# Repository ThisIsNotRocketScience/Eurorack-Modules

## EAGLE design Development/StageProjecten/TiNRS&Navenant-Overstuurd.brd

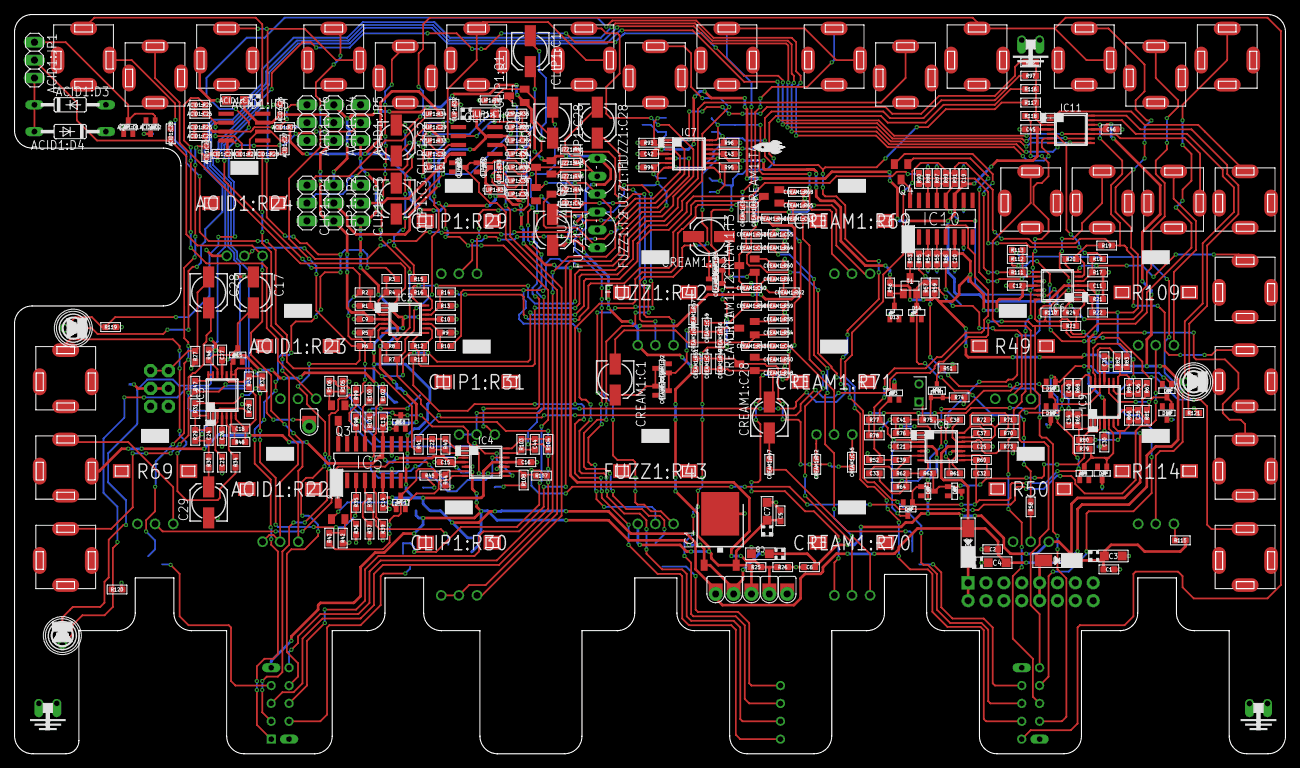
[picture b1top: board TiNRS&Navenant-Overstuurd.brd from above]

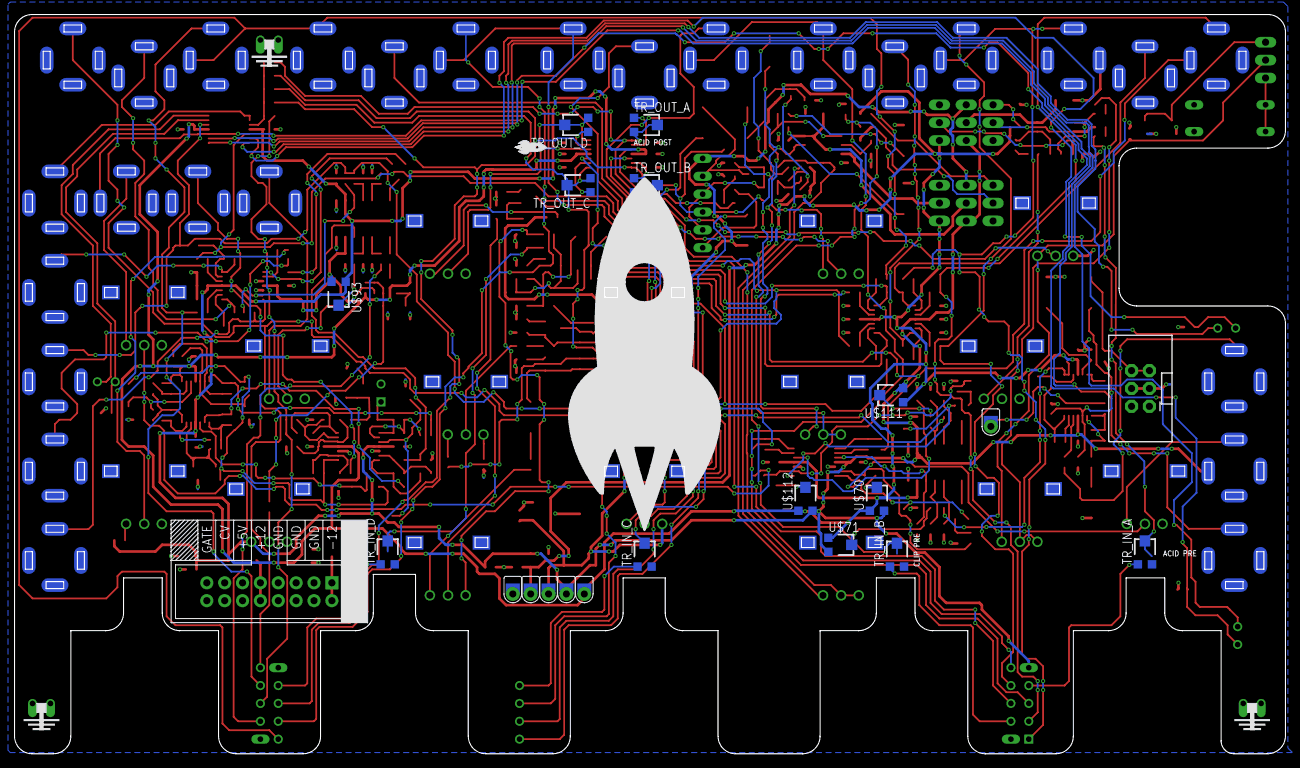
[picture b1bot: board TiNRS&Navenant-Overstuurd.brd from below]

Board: 2 copper layers, 180.7 x 105.1 mm, 375 parts (17 on the bottom side), 216 nets.

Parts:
ACID1:C7: 10uF; CASE-A_3216
ACID1:C22, ACID1:C28: 1nF; C0603
ACID1:C23: 10nF; C0603
ACID1:C24, ACID1:C25: 100n; C0603
ACID1:C26: 47nF; C0603
ACID1:C27: 1uF; C0603
ACID1:D1, ACID1:D2: BAS16W; SOT-323
ACID1:D3, ACID1:D4: 1N4148DO35-10; DO35-10
ACID1:IC5: UA741D; SO08
ACID1:JP1: GERMANIUMSELECTOR; 1X03
ACID1:JP4: ACID+; 1X03
ACID1:JP5: ACID-; 1X03
ACID1:JP6: ACIDBIAS; 1X03
ACID1:R22: 10KB; ALPS_POT_SQUAREHOLES
ACID1:R23: 1MC; ALPS_POT_SQUAREHOLES
ACID1:R24: 10KA; ALPS_POT_SQUAREHOLES
ACID1:R25: 10K; R0603
ACID1:R26: 4.7K; R0603
ACID1:R27, ACID1:R72: 1M; R0603
ACID1:R28: 5.6K; R0603
C1, C2, C5, C6, C9, C10, C11, C12, C13, C14, C15, C16, C19, C20, C21, C25, C26, C27, C30, C31, C38, C42, C43, C45, C46: 100n; C0603
C3, C4, C7, C8: 10u; CASE-A_3216
C17, C28, C29: 10uF; 153CLV-0505
C18, C22, C23, C44: 10pF; C0603
C24: 47pF; C0603
C32, C34, C35, C36, C37: 33p; C0603
C33: 220p; C0603
C39: 680n; C0603
C40, C41: 33p FIX; C0603
CLIP1:C1, CLIP1:C3: 4.7uF; 153CLV-0505
CLIP1:C2: 2.2uF; 153CLV-0505
CLIP1:C4, CLIP1:C25: 100n; C0603
CLIP1:C7: 10uF; CASE-A_3216
CLIP1:C28: 1uF; 153CLV-0505
CLIP1:C29, CLIP1:C36: 22nF; C0603
CLIP1:C30: 1nF; C0603
CLIP1:C31: 100pF; C0603
CLIP1:C35: 3.3nF; C0603
CLIP1:D1, CLIP1:D2: BAS16W; SOT-323
CLIP1:IC6: UA741D; SO08
CLIP1:JP1: CLIPBIAS; 1X03
CLIP1:JP2: CLIP+; 1X03
CLIP1:JP3: CLIP-; 1X03
CLIP1:Q1: SST201; SOT23
CLIP1:R29, CLIP1:R30, CLIP1:R31: 100KA; ALPS_POT_SQUAREHOLES
CLIP1:R32, CLIP1:R34, CLIP1:R39: 1M; R0603
CLIP1:R33, CLIP1:R37: 1K; R0603
CLIP1:R35: 560R; R0603
CLIP1:R36: 47R; R0603
CLIP1:R38: 1.5K; R0603
CLIP1:R40: 10K; R0603
CREAM1:C1, CREAM1:C2, CREAM1:C28: 1uF; 153CLV-0505
CREAM1:C44, CREAM1:C47, CREAM1:C50: 470pF; C0603
CREAM1:C45: 1uF; C0603
CREAM1:C46, CREAM1:C49, CREAM1:C53, CREAM1:C54: 100nF; C0603
CREAM1:C52: 4nF; C0603
CREAM1:C55: 10nF; C0603
CREAM1:D1, CREAM1:D2, CREAM1:D3, CREAM1:D4: BAS16W; SOT-323
CREAM1:R47, CREAM1:R63: 39K; R0603
CREAM1:R48: 47K; R0603
CREAM1:R49, CREAM1:R56, CREAM1:R61: 470K; R0603
CREAM1:R50: 100R; R0603
CREAM1:R51, CREAM1:R53, CREAM1:R57, CREAM1:R58, CREAM1:R62: 10K; R0603
CREAM1:R52: 1K; R0603
CREAM1:R54, CREAM1:R59, CREAM1:R65: 100K; R0603
CREAM1:R55, CREAM1:R60: 150R; R0603
CREAM1:R64: 22K; R0603
CREAM1:R66: 430K; R0603
CREAM1:R67: 15K; R0603
CREAM1:R68: 3.3K; R0603
CREAM1:R69, CREAM1:R70, CREAM1:R71: 100KB; ALPS_POT_SQUAREHOLES
CREAM1:T1, CREAM1:T2, CREAM1:T3, CREAM1:T4: 2n3904; SOT23-BEC
D1, D2: 1n4001; DO-214AC
D3, D4, D5, D6, D7, D8, D9, D10, D11, D12, D13, D14, D15, D17, D18: BAS16W; SOT-323
D16, D19, D20: 3MMLED
FUZZ1:C1: 20uF; 153CLV-0505
FUZZ1:C28: 2.2uF; 153CLV-0505
FUZZ1:C42: 10nF; C0603
FUZZ1:Q1, FUZZ1:Q2: MMBT3906LT1SMD; SOT23-BEC
FUZZ1:R41: 100K; R0603
FUZZ1:R42: 500KA; ALPS_POT_SQUAREHOLES
FUZZ1:R43: 1KB; ALPS_POT_SQUAREHOLES
FUZZ1:R44: 8.2K; R0603
FUZZ1:R45: 33K; R0603
FUZZ1:R46: 470R; R0603
FUZZ1:T1, FUZZ1:T2: TO92-EBC
IC1: 7809DT; TO252
IC2, IC3, IC4, IC6, IC7, IC8, IC9, IC11: TL074TSSOP14; TSSOP14
IC5, IC10: LM13700M; SO16
J1, J3, J4, J5, J6, J7, J8, J9, J10, J11, J12, J13, J14, J15, J16, J17, J18, J19, J20, J21, J22, J23, J24, J25, J26, J27: JACK; 3.5MM-JACK-SWITCH-13MM-NOHOLES
J2: POWERSHROUDED; POWER_16_SHROUDED
PCB1: EURORACK_PCB5STOMP; EURORACK36HP_5STOMP
Q1, Q3, Q4: MMBT3906LT1SMD; SOT23-BEC
R1, R2, R3, R4, R5, R6, R7, R8, R9, R10, R11, R12, R13, R14, R15, R16, R17, R18, R19, R20, R21, R22, R23, R24, R25, R26, R34, R48: 100k; R0603
R27: 1M; R0603
R28: 150K; R0603
R29, R42, R60, R72, R74, R105: 10K; R0603
R30: 470R; R0603
R31, R41, R47, R104: 1K; R0603
R32, R33, R38, R39, R40, R43, R44, R64, R65, R66, R67, R68, R71, R76, R78, R80, R83, R84, R92, R97, R101, R102, R103, R106, R107, R116, R117, R118: 100K; R0603
R35, R98: 4.7K; R0603
R36, R37, R99, R100: 10R; R0603
R45, R46, R108: 330K; R0603
R49, R69, R109: 100KB; ALPS_POT_SQUAREHOLES
R50, R114: 10KB; ALPS_POT_SQUAREHOLES
R51: 14; R0603
R52, R56: 470K; R0603
R53: 4K7; R0603
R54, R55, R70: 100; R0603
R57: 22K; R0603
R58, R62, R63, R77, R79, R81, R82: 33K; R0603
R59: 4M7; R0603
R61: 47K; R0603
R73: 220K; R0603
R75: 6K8; R0603
R85: 27k; R0603
R86: 150k; R0603
R87, R88: 1k; R0603
R89, R90: 200k; R0603
R91, R110: 47k; R0603
R93, R94, R95, R96: 4.7k; R0603
R111: 2.2k; R0603
R112, R113: 18k; R0603
R115: 14k; R0603
R119, R120, R121: 1.2K; R0603
T1: 3906; SOT23-BEC
TR_IN_A: 50k; TC33X
TR_IN_B: 50k; TC33X
TR_IN_C: 50k; TC33X
TR_IN_D: 50k; TC33X
TR_OUT_A: 50k; TC33X
TR_OUT_B: 50k; TC33X
TR_OUT_C: 50k; TC33X
TR_OUT_D: 50k; TC33X
U$13, U$15, U$41, U$42, U$43, U$44: VOLTAGETESTPAD; POWERTESTPAD
U$22: 5STOMPBOARD; BYPASSBOARD
U$23: HEADPHONEHOLE_BIGGAP; HEADPHONEHOLE_GAP
U$48, U$49, U$50: GNDLOOP; GROUNDLOOP
U$68: HEADPHONE; 2X3-SHROUDED
U$70, U$71, U$111, U$112: 100k; TC33X
U$74: BAT54S; SOT23
U$92: TESTPOINT_DUAL_PTH; TESTPAD_DUAL_PTH
U$93: 50K; TC33X
U$94, U$95: TINRS_ARTWORKTINYDATE; JUSTATINYROCKET_DATECODE
U$96: ROCKET-5CM

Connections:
4.5V: ACID1:R72.2, CLIP1:R34.2, R25.1, R26.2, U$44.P$1, U$44.P$2, U$44.P$3
9V: ACID1:JP4.1, C5.2, C7.+, CLIP1:JP2.1, CLIP1:Q1.1, CREAM1:R51.1, CREAM1:R57.1, CREAM1:R62.1, CREAM1:R66.2, CREAM1:R67.2, FUZZ1:C1.+, FUZZ1:Q1.E, FUZZ1:R42.P$1, FUZZ1:R43.P$1, FUZZ1:T1.E, IC1.2, R25.2, U$42.P$1, U$42.P$2, U$42.P$3
12V: ACID1:JP4.3, C1.2, C3.+, C6.2, C8.+, C9.2, C11.2, C13.2, C15.2, C19.2, C21.2, C26.2, C30.2, C42.2, C45.2, CLIP1:JP2.3, D1.2, IC1.1, IC2.4, IC3.4, IC4.4, IC5.11, IC6.4, IC7.4, IC8.4, IC9.4, IC10.11, IC11.4, J21.SWITCH_B@1, J21.SWITCH_T@3, R50.P$3, R115.1, U$13.P$1, U$13.P$2, U$13.P$3, U$22.12V, U$70.3, U$71.3, U$93.1, U$111.3, U$112.3
-12V: ACID1:JP5.3, C2.1, C4.-, C10.1, C12.1, C14.1, C16.1, C20.1, C25.1, C27.1, C31.1, C43.1, C46.1, CLIP1:JP3.3, D2.1, IC2.11, IC3.11, IC4.11, IC5.6, IC6.11, IC7.11, IC8.11, IC9.11, IC10.6, IC11.11, R56.2, R59.1, U$41.P$1, U$41.P$2, U$41.P$3, U$70.1, U$71.1, U$93.3, U$111.1, U$112.1
ACID1:ACIDNE: ACID1:C24.1, ACID1:IC5.4, ACID1:JP5.2
ACID1:ACIDPL: ACID1:C7.+, ACID1:C25.1, ACID1:IC5.7, ACID1:JP4.2
ACID1:ACIDVI: ACID1:IC5.3, ACID1:JP6.2, ACID1:R25.1
ACID1:N$2: ACID1:D3.C, ACID1:D4.A, ACID1:JP1.3
ACID1:N$3: ACID1:D1.CATHODE, ACID1:D2.ANODE, ACID1:JP1.1
ACID1:N$20: ACID1:C23.2, ACID1:R25.2
ACID1:N$22: ACID1:C26.2, ACID1:IC5.2, ACID1:R27.1
ACID1:N$23: ACID1:C26.1, ACID1:R26.1
ACID1:N$32: ACID1:C27.1, ACID1:IC5.6, ACID1:R27.2
ACID1:N$33: ACID1:R23.P$3, ACID1:R26.2
ACID1:N$34: ACID1:C28.2, ACID1:JP1.2, ACID1:R22.P$3, ACID1:R24.P$3
ACID1:N$35: ACID1:C27.2, ACID1:R28.2
ACID1:N$36: ACID1:R22.P$1, ACID1:R22.P$2, ACID1:R28.1
ACID1:TO4.5V: ACID1:JP6.1, ACID1:R72.1
BIASINPUT: J23.TIP_B@1, J23.TIP_T@3, R61.2
BIASMAINLINE: C32.1, D4.ANODE, D6.ANODE, D8.ANODE, D9.ANODE, D10.ANODE, IC8.8, R60.1
CLIP1:CLIPNE: CLIP1:C4.1, CLIP1:IC6.4, CLIP1:JP3.2
CLIP1:CLIPPL: CLIP1:C7.+, CLIP1:C25.1, CLIP1:IC6.7, CLIP1:JP2.2
CLIP1:CLIPVI: CLIP1:C29.2, CLIP1:JP1.2, CLIP1:R33.1
CLIP1:N$38: CLIP1:C30.2, CLIP1:IC6.3, CLIP1:R33.2
CLIP1:N$41: CLIP1:JP1.1, CLIP1:R34.1
CLIP1:N$42: CLIP1:C31.1, CLIP1:IC6.2, CLIP1:R31.P$1, CLIP1:R31.P$2, CLIP1:R35.2, CLIP1:R36.2
CLIP1:N$43: CLIP1:C1.+, CLIP1:C31.2, CLIP1:IC6.6, CLIP1:R31.P$3
CLIP1:N$44: CLIP1:C1.-, CLIP1:R37.1
CLIP1:N$45: CLIP1:D1.CATHODE, CLIP1:D2.ANODE, CLIP1:R30.P$1, CLIP1:R30.P$2, CLIP1:R37.2
CLIP1:N$46: CLIP1:R30.P$3, CLIP1:R38.1
CLIP1:N$47: CLIP1:C2.+, CLIP1:R36.1
CLIP1:N$48: CLIP1:C3.+, CLIP1:R35.1
CLIP1:N$49: CLIP1:C35.1, CLIP1:C36.1, CLIP1:R38.2
CLIP1:N$50: CLIP1:C36.2, CLIP1:Q1.3, CLIP1:R39.2
CLIP1:N$51: CLIP1:C28.+, CLIP1:Q1.2, CLIP1:R40.2
CLIP1:N$52: CLIP1:C28.-, CLIP1:R29.P$3
CREAM1:N$1: CREAM1:C28.-, CREAM1:R47.2
CREAM1:N$61: CREAM1:C28.+, CREAM1:C44.1, CREAM1:R48.2, CREAM1:R49.2, CREAM1:T1.B
CREAM1:N$62: CREAM1:R50.1, CREAM1:T1.E
CREAM1:N$63: CREAM1:C44.2, CREAM1:C45.1, CREAM1:R49.1, CREAM1:R51.2, CREAM1:T1.C
CREAM1:N$64: CREAM1:C45.2, CREAM1:R71.P$3
CREAM1:N$65: CREAM1:C1.-, CREAM1:C47.1, CREAM1:R53.2, CREAM1:R54.2, CREAM1:R56.2, CREAM1:T2.B
CREAM1:N$66: CREAM1:C1.+, CREAM1:D1.ANODE, CREAM1:D2.CATHODE
CREAM1:N$67: CREAM1:R55.2, CREAM1:T2.E
CREAM1:N$68: CREAM1:C47.2, CREAM1:C49.1, CREAM1:D1.CATHODE, CREAM1:D2.ANODE, CREAM1:R56.1, CREAM1:R57.2, CREAM1:T2.C
CREAM1:N$69: CREAM1:C49.2, CREAM1:R58.1
CREAM1:N$70: CREAM1:C2.-, CREAM1:C50.1, CREAM1:R58.2, CREAM1:R59.2, CREAM1:R61.2, CREAM1:T3.B
CREAM1:N$71: CREAM1:R60.2, CREAM1:T3.E
CREAM1:N$72: CREAM1:C50.2, CREAM1:C52.1, CREAM1:D3.ANODE, CREAM1:D4.CATHODE, CREAM1:R61.1, CREAM1:R62.2, CREAM1:R63.1, CREAM1:T3.C
CREAM1:N$73: CREAM1:C53.1, CREAM1:R70.P$2
CREAM1:N$74: CREAM1:C55.2, CREAM1:R63.2, CREAM1:R70.P$1
CREAM1:N$75: CREAM1:C52.2, CREAM1:R64.1, CREAM1:R70.P$3
CREAM1:N$76: CREAM1:C2.+, CREAM1:D3.CATHODE, CREAM1:D4.ANODE
CREAM1:N$77: CREAM1:C53.2, CREAM1:R65.2, CREAM1:R66.1, CREAM1:T4.B
CREAM1:N$78: CREAM1:C54.1, CREAM1:R67.1, CREAM1:T4.C
CREAM1:N$79: CREAM1:R68.2, CREAM1:T4.E
CREAM1:N$80: CREAM1:C54.2, CREAM1:R69.P$3
CREAM1:N$84: CREAM1:R52.1, CREAM1:R71.P$1
CREAM1:N$85: CREAM1:C46.2, CREAM1:R53.1
CREAM1:N$86: CREAM1:C46.1, CREAM1:R71.P$2
CROSSFADER_OUT: IC6.14, J26.TIP_B@1, J26.TIP_T@3, R110.1
CV_IN: J25.TIP_B@1, J25.TIP_T@3, R112.2
ENVELOPE_OUT: IC11.10, J1.SWITCH_B@1, J1.SWITCH_T@3, J24.TIP_B@1, J24.TIP_T@3, R47.1
EURORACK_IN: J20.TIP_B@1, J20.TIP_T@3, R34.1
FUZZ1:N$53: FUZZ1:Q2.E, FUZZ1:R41.1, FUZZ1:R43.P$3, FUZZ1:T2.E
FUZZ1:N$54: FUZZ1:C28.-, FUZZ1:Q1.B, FUZZ1:R41.2, FUZZ1:T1.B
FUZZ1:N$55: FUZZ1:Q1.C, FUZZ1:Q2.B, FUZZ1:R45.2, FUZZ1:T1.C, FUZZ1:T2.B
FUZZ1:N$56: FUZZ1:C1.-, FUZZ1:R43.P$2
FUZZ1:N$57: FUZZ1:C42.2, FUZZ1:R42.P$3
FUZZ1:N$58: FUZZ1:C42.1, FUZZ1:R44.1, FUZZ1:R46.2
FUZZ1:N$59: FUZZ1:Q2.C, FUZZ1:R44.2, FUZZ1:T2.C
GND: ACID1:C7.-, ACID1:C22.2, ACID1:C24.2, ACID1:C25.2, ACID1:C28.1, ACID1:D1.ANODE, ACID1:D2.CATHODE, ACID1:D3.A, ACID1:D4.C, ACID1:JP5.1, ACID1:R23.P$1, ACID1:R23.P$2, ACID1:R24.P$1, C1.1, C2.2, C3.-, C4.+, C5.1, C6.1, C7.-, C8.-, C9.1, C10.2, C11.1, C12.2, C13.1, C14.2, C15.1, C16.2, C17.-, C19.1, C20.2, C21.1, C23.1, C25.2, C26.1, C27.2, C29.-, C30.1, C31.2, C42.1, C43.2, C45.1, C46.2, CLIP1:C2.-, CLIP1:C3.-, CLIP1:C4.2, CLIP1:C7.-, CLIP1:C25.2, CLIP1:C30.1, CLIP1:C35.2, CLIP1:D1.ANODE, CLIP1:D2.CATHODE, CLIP1:JP3.1, CLIP1:R29.P$1, CLIP1:R32.2, CLIP1:R39.1, CLIP1:R40.1, CREAM1:C55.1, CREAM1:R48.1, CREAM1:R50.2, CREAM1:R52.2, CREAM1:R54.1, CREAM1:R55.1, CREAM1:R59.1, CREAM1:R60.1, CREAM1:R64.2, CREAM1:R65.1, CREAM1:R68.1, CREAM1:R69.P$1, D3.CATHODE, D5.CATHODE, D7.CATHODE, D11.CATHODE, D12.CATHODE, D13.ANODE, D14.ANODE, FUZZ1:R45.1, FUZZ1:R46.1, IC1.3, IC4.5, IC4.10, IC5.7, IC5.10, IC6.10, IC6.12, IC8.5, IC8.10, IC10.7, IC10.10, J1.RING_B@1, J1.RING_T@3, J2.3, J2.4, J2.5, J2.6, J2.7, J2.8, J3.RING_B@1, J3.RING_T@3, J4.RING_B@1, J4.RING_T@3, J5.RING_B@1, J5.RING_T@3, J6.RING_B@1, J6.RING_T@3, J7.RING_B@1, J7.RING_T@3, J8.RING_B@1, J8.RING_T@3, J9.RING_B@1, J9.RING_T@3, J10.RING_B@1, J10.RING_T@3, J11.RING_B@1, J11.RING_T@3, J12.RING_B@1, J12.RING_T@3, J13.RING_B@1, J13.RING_T@3, J14.RING_B@1, J14.RING_T@3, J15.RING_B@1, J15.RING_T@3, J16.RING_B@1, J16.RING_T@3, J17.RING_B@1, J17.RING_T@3, J18.RING_B@1, J18.RING_T@3, J19.RING_B@1, J19.RING_T@3, J20.RING_B@1, J20.RING_T@3, J20.SWITCH_B@1, J20.SWITCH_T@3, J21.RING_B@1, J21.RING_T@3, J22.RING_B@1, J22.RING_T@3, J23.RING_B@1, J23.RING_T@3, J23.SWITCH_B@1, J23.SWITCH_T@3, J24.RING_B@1, J24.RING_T@3, J25.RING_B@1, J25.RING_T@3, J25.SWITCH_B@1, J25.SWITCH_T@3, J26.RING_B@1, J26.RING_T@3, J27.RING_B@1, J27.RING_T@3, R1.2, R5.2, R9.2, R13.2, R17.2, R21.2, R26.1, R27.1, R28.1, R36.1, R37.2, R39.2, R42.1, R46.1, R49.P$1, R50.P$1, R51.2, R52.2, R54.1, R55.1, R69.P$1, R72.2, R73.1, R74.1, R87.1, R88.1, R93.2, R94.2, R95.2, R96.2, R99.1, R100.2, R102.2, R105.1, R109.P$1, R114.P$1, R119.1, R120.1, R121.1, TR_IN_A.3, TR_IN_B.3, TR_IN_C.3, TR_IN_D.3, U$22.GND, U$22.GND2, U$22.GND3, U$43.P$1, U$43.P$2, U$43.P$3, U$48.P$1, U$48.P$2, U$49.P$1, U$49.P$2, U$50.P$1, U$50.P$2, U$68.3, U$68.4, U$92.P$2
GUITAR_IN: C28.-, R27.2, U$68.5, U$68.6
GUITAR_OUT: R31.2, R32.2, U$15.P$1, U$15.P$2, U$15.P$3
INPUT_A: J6.TIP_B@1, J6.TIP_T@3, R2.2, U$22.P$3
INPUT_B: J4.TIP_B@1, J4.TIP_T@3, R6.2, U$22.P$7
INPUT_C: J11.TIP_B@1, J11.TIP_T@3, R10.2, U$22.P$11
INPUT_D: J14.TIP_B@1, J14.TIP_T@3, R14.2, U$22.P$15
INPUT_E: J17.TIP_B@1, J17.TIP_T@3, R22.2, U$22.P$19
INPUT_WS: R85.2, U$22.P$20
MIX_OUT: D15.ANODE, IC3.8, IC3.9, R35.1
unnamed: IC7.2, R93.1, TR_OUT_A.1
unnamed: D1.1, J2.9, J2.10
unnamed: D2.2, J2.1, J2.2
unnamed: IC11.1, IC11.2, J27.TIP_B@1, J27.TIP_T@3
unnamed: TR_IN_A.1, U$22.P$4
unnamed: ACID1:R24.P$2, IC7.3
unnamed: TR_IN_B.1, U$22.P$8
unnamed: TR_IN_C.1, U$22.P$12
unnamed: FUZZ1:C28.+, TR_IN_C.2
unnamed: IC11.3, R92.2, R97.2, R116.2, R117.2, R118.2
unnamed: IC7.9, R95.1, TR_OUT_C.1
unnamed: CLIP1:C29.1, CLIP1:R32.1, TR_IN_B.2
unnamed: D16.+, IC11.6, R119.2
unnamed: C23.2, C28.+, IC3.3, R28.2
unnamed: IC2.3, R1.1, R2.1
unnamed: IC6.9, R111.2, R112.1, R113.1
unnamed: C24.1, IC3.1, R29.2, R31.1
unnamed: IC2.1, J8.TIP_B@1, J8.TIP_T@3, R4.1
unnamed: IC2.5, R5.1, R6.1
unnamed: IC2.6, R7.1, R8.2
unnamed: Q4.E, R111.1
unnamed: IC6.8, Q4.B
unnamed: IC2.7, J5.TIP_B@1, J5.TIP_T@3, R8.1
unnamed: IC2.10, R9.1, R10.1
unnamed: IC2.9, R11.1, R12.2
unnamed: R114.P$3, R115.2
unnamed: R113.2, R114.P$2
unnamed: IC2.8, J12.TIP_B@1, J12.TIP_T@3, R12.1
unnamed: IC2.12, R13.1, R14.1
unnamed: IC2.13, R15.1, R16.2
unnamed: IC7.6, R94.1, TR_OUT_B.1
unnamed: D16.-, IC11.7
unnamed: IC2.14, J15.TIP_B@1, J15.TIP_T@3, R16.1
unnamed: IC6.5, R17.1, R18.1
unnamed: IC6.6, R19.1, R20.2
unnamed: D19.+, IC11.9, R120.2
unnamed: CLIP1:R29.P$2, IC7.5
unnamed: IC6.7, J10.TIP_B@1, J10.TIP_T@3, R20.1
unnamed: IC6.3, R21.1, R22.1
unnamed: IC6.2, R23.1, R24.2
unnamed: ACID1:C22.1, ACID1:C23.1, TR_IN_A.2
unnamed: D19.-, IC11.8
unnamed: IC6.1, J18.TIP_B@1, J18.TIP_T@3, R24.1
unnamed: C24.2, IC3.2, R29.1, R30.2
unnamed: C29.+, R30.1
unnamed: C18.2, IC3.7, R33.2, R48.2
unnamed: IC3.5, R34.2
unnamed: IC5.4, R37.1, R38.1
unnamed: IC5.3, R35.2, R36.2
unnamed: IC4.3, IC5.5, R39.1
unnamed: C22.1, IC4.2, R40.1
unnamed: C22.2, IC4.1, R40.2, R41.1
unnamed: R38.2, U$71.2
unnamed: D17.ANODE, IC4.7, Q1.B
unnamed: D17.CATHODE, IC4.6, R43.1, R44.2, R45.2
unnamed: Q1.E, R42.2, R43.2
unnamed: IC5.1, Q1.C
unnamed: R45.1, U$70.2
unnamed: R44.1, R69.P$2
unnamed: IC3.13, IC3.14, R47.2
unnamed: C17.+, D15.CATHODE, IC3.12, R46.2
unnamed: C18.1, IC3.6, R48.1
unnamed: R51.1, U$74.P$3
unnamed: C32.2, IC8.9, R60.2, R61.1
unnamed: R49.P$2, R57.2
unnamed: J22.TIP_B@1, J22.TIP_T@3, R49.P$3
unnamed: D14.CATHODE, R57.1, R58.1, R59.2, T1.E
unnamed: R50.P$2, R58.2
unnamed: C38.2, R74.2, R75.2, U$74.P$1, U$74.P$2
unnamed: C33.1, IC8.7, R62.1, R63.2, R64.2
unnamed: C33.2, C39.2, IC8.6, R62.2
unnamed: C39.1, IC10.5, R52.1
unnamed: D5.ANODE, D6.CATHODE, IC9.3, R63.1
unnamed: C34.1, IC9.1, R65.1, R79.2, R80.2
unnamed: D7.ANODE, D8.CATHODE, IC9.5, R79.1
unnamed: C34.2, IC9.2, R64.1, R65.2
unnamed: C35.2, IC9.6, R66.2, R80.1
unnamed: C35.1, IC9.7, R66.1, R67.2, R81.2
unnamed: D9.CATHODE, D12.ANODE, IC9.10, R81.1
unnamed: C36.1, IC9.8, R82.2, R83.2, R84.1
unnamed: C36.2, IC9.9, R67.1, R84.2
unnamed: D10.CATHODE, D11.ANODE, IC9.12, R82.1
unnamed: C40.2, IC9.13, R68.2, R83.1
unnamed: C40.1, IC9.14, R68.1, R77.1, R78.1
unnamed: D3.ANODE, D4.CATHODE, IC8.3, R77.2
unnamed: C41.2, IC8.2, R76.1, R78.2
unnamed: C41.1, IC8.1, R75.1, R76.2, U$92.P$1
unnamed: C38.1, IC8.12, R73.2
unnamed: C37.1, IC8.14, R70.2
unnamed: C37.2, IC8.13, R71.2, R72.1
unnamed: D13.CATHODE, R56.1, T1.B
unnamed: R53.1, T1.C
unnamed: IC10.1, R53.2
unnamed: IC10.3, R54.2, R85.1
unnamed: R86.2, U$93.2
unnamed: IC10.4, R55.2, R86.1
unnamed: IC10.13, R87.2, R89.1
unnamed: IC10.14, R88.2, R90.1
unnamed: TR_IN_D.1, U$22.P$16
unnamed: CREAM1:R47.1, TR_IN_D.2
unnamed: IC7.13, R96.1, TR_OUT_D.1
unnamed: CREAM1:R69.P$2, IC7.12
unnamed: FUZZ1:R42.P$2, IC7.10
unnamed: D20.+, IC11.13, R121.2
unnamed: D20.-, IC11.14
unnamed: IC5.13, R100.1, R101.1
unnamed: IC5.14, R98.2, R99.2
unnamed: IC4.12, IC5.12, R102.1
unnamed: C44.1, IC4.13, R103.1
unnamed: C44.2, IC4.14, R103.2, R104.1
unnamed: R101.2, U$111.2
unnamed: D18.ANODE, IC4.8, Q3.B
unnamed: D18.CATHODE, IC4.9, R106.1, R107.2, R108.2
unnamed: Q3.E, R105.2, R106.2
unnamed: IC5.16, Q3.C
unnamed: R108.1, U$112.2
unnamed: R107.1, R109.P$2
unnamed: IC2.2, R3.1, R4.2
OPAMP_A: IC7.1, R92.1, TR_OUT_A.2, TR_OUT_A.3, U$22.P$2
OPAMP_B: IC7.7, R97.1, TR_OUT_B.2, TR_OUT_B.3, U$22.P$6
OPAMP_C: IC7.8, R116.1, TR_OUT_C.2, TR_OUT_C.3, U$22.P$10
OPAMP_D: IC7.14, R117.1, TR_OUT_D.2, TR_OUT_D.3, U$22.P$14
OTA_CONTROL: IC10.16, Q4.C
OTA_OUT: IC6.13, IC10.12, R91.2, R110.2
OUTPUT_A: J4.SWITCH_B@1, J4.SWITCH_T@3, J7.TIP_B@1, J7.TIP_T@3, R3.2, U$22.P$1
OUTPUT_B: J9.TIP_B@1, J9.TIP_T@3, J11.SWITCH_B@1, J11.SWITCH_T@3, R7.2, U$22.P$5
OUTPUT_C: J13.TIP_B@1, J13.TIP_T@3, J14.SWITCH_B@1, J14.SWITCH_T@3, R11.2, U$22.P$9
OUTPUT_D: J16.TIP_B@1, J16.TIP_T@3, J17.SWITCH_B@1, J17.SWITCH_T@3, R15.2, U$22.P$13
OUTPUT_E: J19.TIP_B@1, J19.TIP_T@3, R23.2, R98.1, U$22.P$17
OUTPUT_WS: R70.1, R71.1, R118.1, U$22.P$18
VCA_CV_IN1: J21.TIP_B@1, J21.TIP_T@3, R69.P$3
VCA_CV_IN2: J1.TIP_B@1, J1.TIP_T@3, R109.P$3
VCA_OUTPUT1: IC11.5, J6.SWITCH_B@1, J6.SWITCH_T@3, R18.2, R41.2, R90.2
VCA_OUTPUT2: IC11.12, J3.TIP_B@1, J3.TIP_T@3, R19.2, R89.2, R91.1, R104.2
VCA_SIG_IN: IC3.10, R32.1, R33.1

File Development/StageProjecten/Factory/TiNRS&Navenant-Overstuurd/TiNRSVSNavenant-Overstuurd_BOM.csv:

Comment,Designator,Footprint,LCSC Part #
100n,"C1, C2, C5, C6, ACID1:C24, ACID1:C25, C9, C10, C11, C12, C26, C27, C13, C14, C15, C16, C19, C20, C21, C25, C30, C31, C38, CLIP1:C4, CLIP1:C25, C42, C43, C45, C46",C0603,
1nF,"ACID1:C22, ACID1:C28, CLIP1:C30",C0603,
10nF,"ACID1:C23, FUZZ1:C42, CREAM1:C55",C0603,
47nF,"ACID1:C26",C0603,
1uF,"ACID1:C27, CREAM1:C45",C0603,
470pF,"CREAM1:C44, CREAM1:C47, CREAM1:C50",C0603,
100nF,"CREAM1:C46, CREAM1:C49, CREAM1:C53, CREAM1:C54",C0603,
4nF,"CREAM1:C52",C0603,
22nF,"CLIP1:C29, CLIP1:C36",C0603,
100pF,"CLIP1:C31",C0603,
3.3nF,"CLIP1:C35",C0603,
10pF,"C23, C22, C18, C44",C0603,
47pF,"C24",C0603,
33p,"C32, C34, C35, C36, C37",C0603,
220p,"C33",C0603,
680n,"C39",C0603,
33p FIX,"C40, C41",C0603,
10u,"C3, C4, C7, C8",CASE-A_3216,
10uF,"ACID1:C7, CLIP1:C7",CASE-A_3216,
1n4001,"D1, D2",DO-214AC,
UA741D,"ACID1:IC5, CLIP1:IC6",SO08,
ACID+,"ACID1:JP4",1X03,
ACID-,"ACID1:JP5",1X03,
CLIPBIAS,"CLIP1:JP1",1X03,
CLIP+,"CLIP1:JP2",1X03,
CLIP-,"CLIP1:JP3",1X03,
ACIDBIAS,"ACID1:JP6",1X03,
GERMANIUMSELECTOR,"ACID1:JP1",1X03,
10KB,"ACID1:R22, R50, R114",ALPS_POT_SQUAREHOLES,
1MC,"ACID1:R23",ALPS_POT_SQUAREHOLES,
10KA,"ACID1:R24",ALPS_POT_SQUAREHOLES,
500KA,"FUZZ1:R42",ALPS_POT_SQUAREHOLES,
1KB,"FUZZ1:R43",ALPS_POT_SQUAREHOLES,
100KB,"CREAM1:R69, CREAM1:R70, CREAM1:R71, R69, R109, R49",ALPS_POT_SQUAREHOLES,
100KA,"CLIP1:R29, CLIP1:R30, CLIP1:R31",ALPS_POT_SQUAREHOLES,
10K,"ACID1:R25, CREAM1:R51, CREAM1:R53, CREAM1:R57, CREAM1:R58, CREAM1:R62, CLIP1:R40, R29, R42, R105, R60, R72, R74",R0603,
4.7K,"ACID1:R26, R35, R98",R0603,
1M,"ACID1:R27, CLIP1:R32, CLIP1:R34, CLIP1:R39, ACID1:R72, R27",R0603,
5.6K,"ACID1:R28",R0603,
100K,"FUZZ1:R41, CREAM1:R54, CREAM1:R59, CREAM1:R65, R32, R33, R38, R39, R40, R43, R44, R101, R102, R103, R106, R107, R64, R65, R66, R67, R68, R71, R76, R78, R80, R83, R84, R92, R97, R116, R117, R118",R0603,
8.2K,"FUZZ1:R44",R0603,
33K,"FUZZ1:R45, R58, R62, R63, R77, R79, R81, R82",R0603,
470R,"FUZZ1:R46, R30",R0603,
39K,"CREAM1:R47, CREAM1:R63",R0603,
47K,"CREAM1:R48, R61",R0603,
470K,"CREAM1:R49, CREAM1:R56, CREAM1:R61, R52, R56",R0603,
100R,"CREAM1:R50",R0603,
1K,"CREAM1:R52, CLIP1:R33, CLIP1:R37, R31, R41, R47, R104",R0603,
150R,"CREAM1:R55, CREAM1:R60",R0603,
22K,"CREAM1:R64, R57",R0603,
430K,"CREAM1:R66",R0603,
15K,"CREAM1:R67",R0603,
3.3K,"CREAM1:R68",R0603,
560R,"CLIP1:R35",R0603,
47R,"CLIP1:R36",R0603,
1.5K,"CLIP1:R38",R0603,
100k,"R1, R2, R3, R4, R5, R6, R7, R8, R9, R10, R11, R12, R13, R14, R15, R16, R17, R18, R19, R20, R21, R22, R23, R24, R25, R26, R34, R48",R0603,
150K,"R28",R0603,
10R,"R36, R37, R99, R100",R0603,
330K,"R45, R46, R108",R0603,
14,"R51",R0603,
4K7,"R53",R0603,
100,"R54, R55, R70",R0603,
4M7,"R59",R0603,
220K,"R73",R0603,
6K8,"R75",R0603,
27k,"R85",R0603,
150k,"R86",R0603,
1k,"R87, R88",R0603,
200k,"R89, R90",R0603,
47k,"R91, R110",R0603,
2.2k,"R111",R0603,
18k,"R112, R113",R0603,
14k,"R115",R0603,
4.7k,"R93, R94, R95, R96",R0603,
1.2K,"R119, R120, R121",R0603,
20uF,"FUZZ1:C1",153CLV-0505,
2.2uF,"FUZZ1:C28, CLIP1:C2",153CLV-0505,
1uF,"CREAM1:C1, CREAM1:C2, CREAM1:C28, CLIP1:C28",153CLV-0505,
4.7uF,"CLIP1:C1, CLIP1:C3",153CLV-0505,
10uF,"C28, C29, C17",153CLV-0505,
MMBT3906LT1SMD,"FUZZ1:Q1, FUZZ1:Q2, Q1, Q3, Q4",SOT23-BEC,
7809DT,"IC1",TO252,
JACK,"J10, J11, J12, J13, J14, J15, J16, J3, J4, J5, J6, J7, J8, J9, J17, J18, J19, J20, J21, J22, J23, J25, J26, J1, J24, J27",3.5MM-JACK-SWITCH-13MM-NOHOLES,
POWERSHROUDED,"J2",POWER_16_SHROUDED,
2n3904,"CREAM1:T1, CREAM1:T2, CREAM1:T3, CREAM1:T4",SOT23-BEC,
EURORACK_PCB5STOMP,"PCB1",EURORACK36HP_5STOMP,
SST201,"CLIP1:Q1",SOT23,
VOLTAGETESTPAD,"U$13, U$41, U$42, U$43, U$44, U$15",POWERTESTPAD,
5STOMPBOARD,"U$22",BYPASSBOARD,
BAS16W,"CREAM1:D1, CREAM1:D2, CREAM1:D3, CREAM1:D4, CLIP1:D1, CLIP1:D2, D3, D4, D5, D6, D7, D8, D9, D10, D11, D12, D13, D14, ACID1:D1, ACID1:D2, D15, D17, D18",SOT-323,
TL074TSSOP14,"IC2, IC6, IC3, IC4, IC8, IC9, IC7, IC11",TSSOP14,
GNDLOOP,"U$48, U$49, U$50",GROUNDLOOP,
LM13700M,"IC5, IC10",SO16,
HEADPHONE,"U$68",2X3-SHROUDED,
100k,"U$70, U$71, U$111, U$112",TC33X,
50K,"U$93",TC33X,
50k,"TR_OUT_A, TR_IN_A, TR_OUT_B, TR_IN_B, TR_OUT_C, TR_IN_C, TR_OUT_D, TR_IN_D",TC33X,
HEADPHONEHOLE_BIGGAP,"U$23",HEADPHONEHOLE_GAP,
BAT54S,"U$74",SOT23,
3906,"T1",SOT23-BEC,
TESTPOINT_DUAL_PTH,"U$92",TESTPAD_DUAL_PTH,
1N4148DO35-10,"ACID1:D3, ACID1:D4",DO35-10,
,"FUZZ1:T1, FUZZ1:T2",TO92-EBC,
,"D16, D19, D20",3MMLED,
TINRS_ARTWORKTINYDATE,"U$94, U$95",JUSTATINYROCKET_DATECODE,
ROCKET-5CM,"U$96",ROCKET-5CM,

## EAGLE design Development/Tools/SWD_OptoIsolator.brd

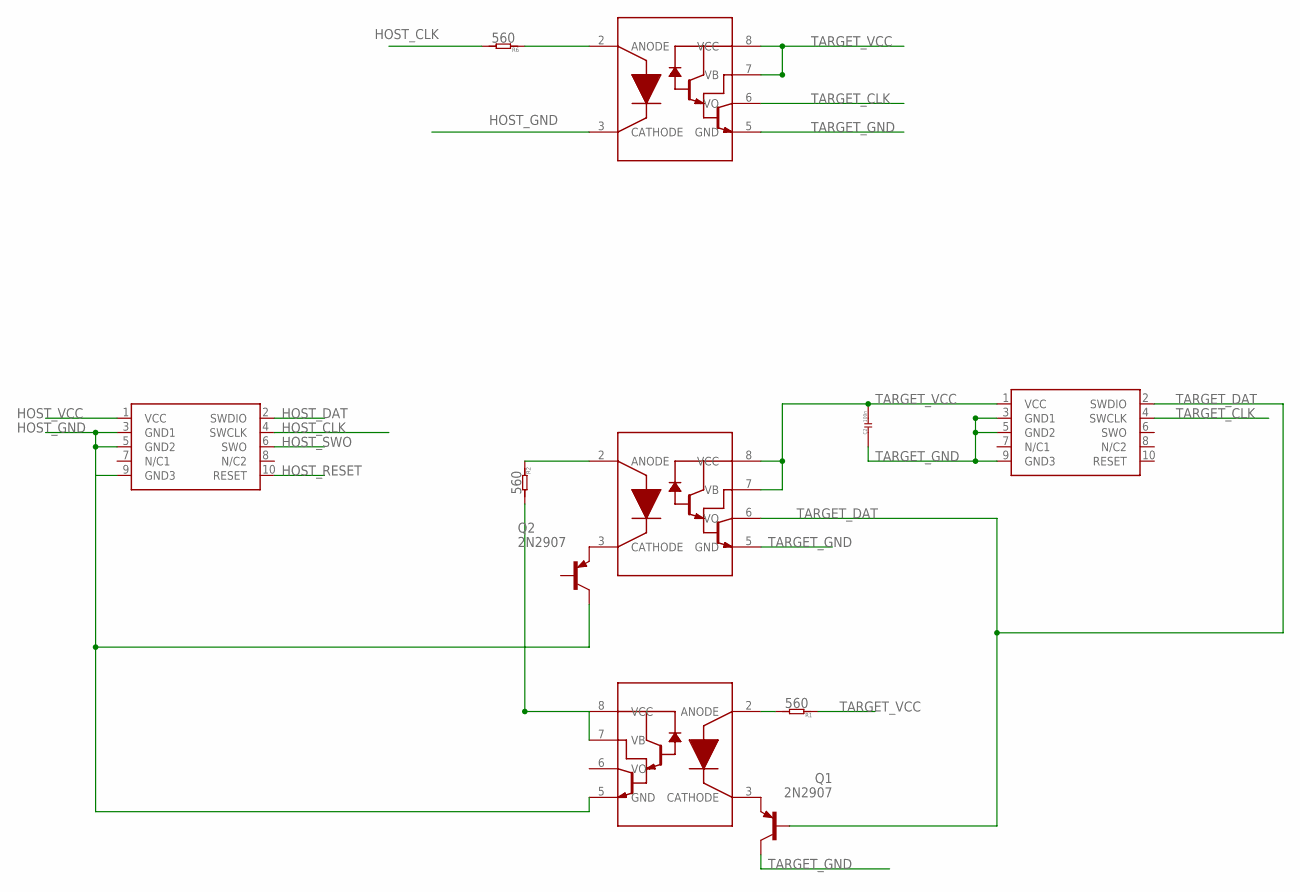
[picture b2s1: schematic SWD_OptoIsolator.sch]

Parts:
C2: 100n; C0603
Q1, Q2: 2N2907; TO92-EBC-OVAL
R1, R2, R6: 560; R0603
SWD1, SWD2: CORTEX_SWD; M50-3600542
U$1, U$2, U$20: 6N139S; 8DIPSMD

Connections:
HOST_CLK: R6.2, SWD1.4 (SWCLK)
HOST_DAT: SWD1.2 (SWDIO)
HOST_GND: Q2.C, SWD1.3 (GND1), SWD1.5 (GND2), SWD1.9 (GND3), U$1.5 (GND), U$2.3 (CATHODE)
HOST_RESET: SWD1.10 (RESET)
HOST_SWO: SWD1.6 (SWO)
HOST_VCC: SWD1.1 (VCC)
unnamed: Q1.E, U$1.3 (CATHODE)
unnamed: R2.2, U$1.7 (VB), U$1.8 (VCC)
unnamed: R2.1, U$20.2 (ANODE)
unnamed: R1.2, U$1.2 (ANODE)
unnamed: Q2.E, U$20.3 (CATHODE)
unnamed: R6.1, U$2.2 (ANODE)
TARGET_CLK: SWD2.4 (SWCLK), U$2.6 (VO)
TARGET_DAT: Q1.B, SWD2.2 (SWDIO), U$20.6 (VO)
TARGET_GND: C2.1, Q1.C, SWD2.3 (GND1), SWD2.5 (GND2), SWD2.9 (GND3), U$2.5 (GND), U$20.5 (GND)
TARGET_VCC: C2.2, R1.1, SWD2.1 (VCC), U$2.7 (VB), U$2.8 (VCC), U$20.7 (VB), U$20.8 (VCC)

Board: 2 copper layers, 11 parts (0 on the bottom side), 12 nets, no tracks yet.

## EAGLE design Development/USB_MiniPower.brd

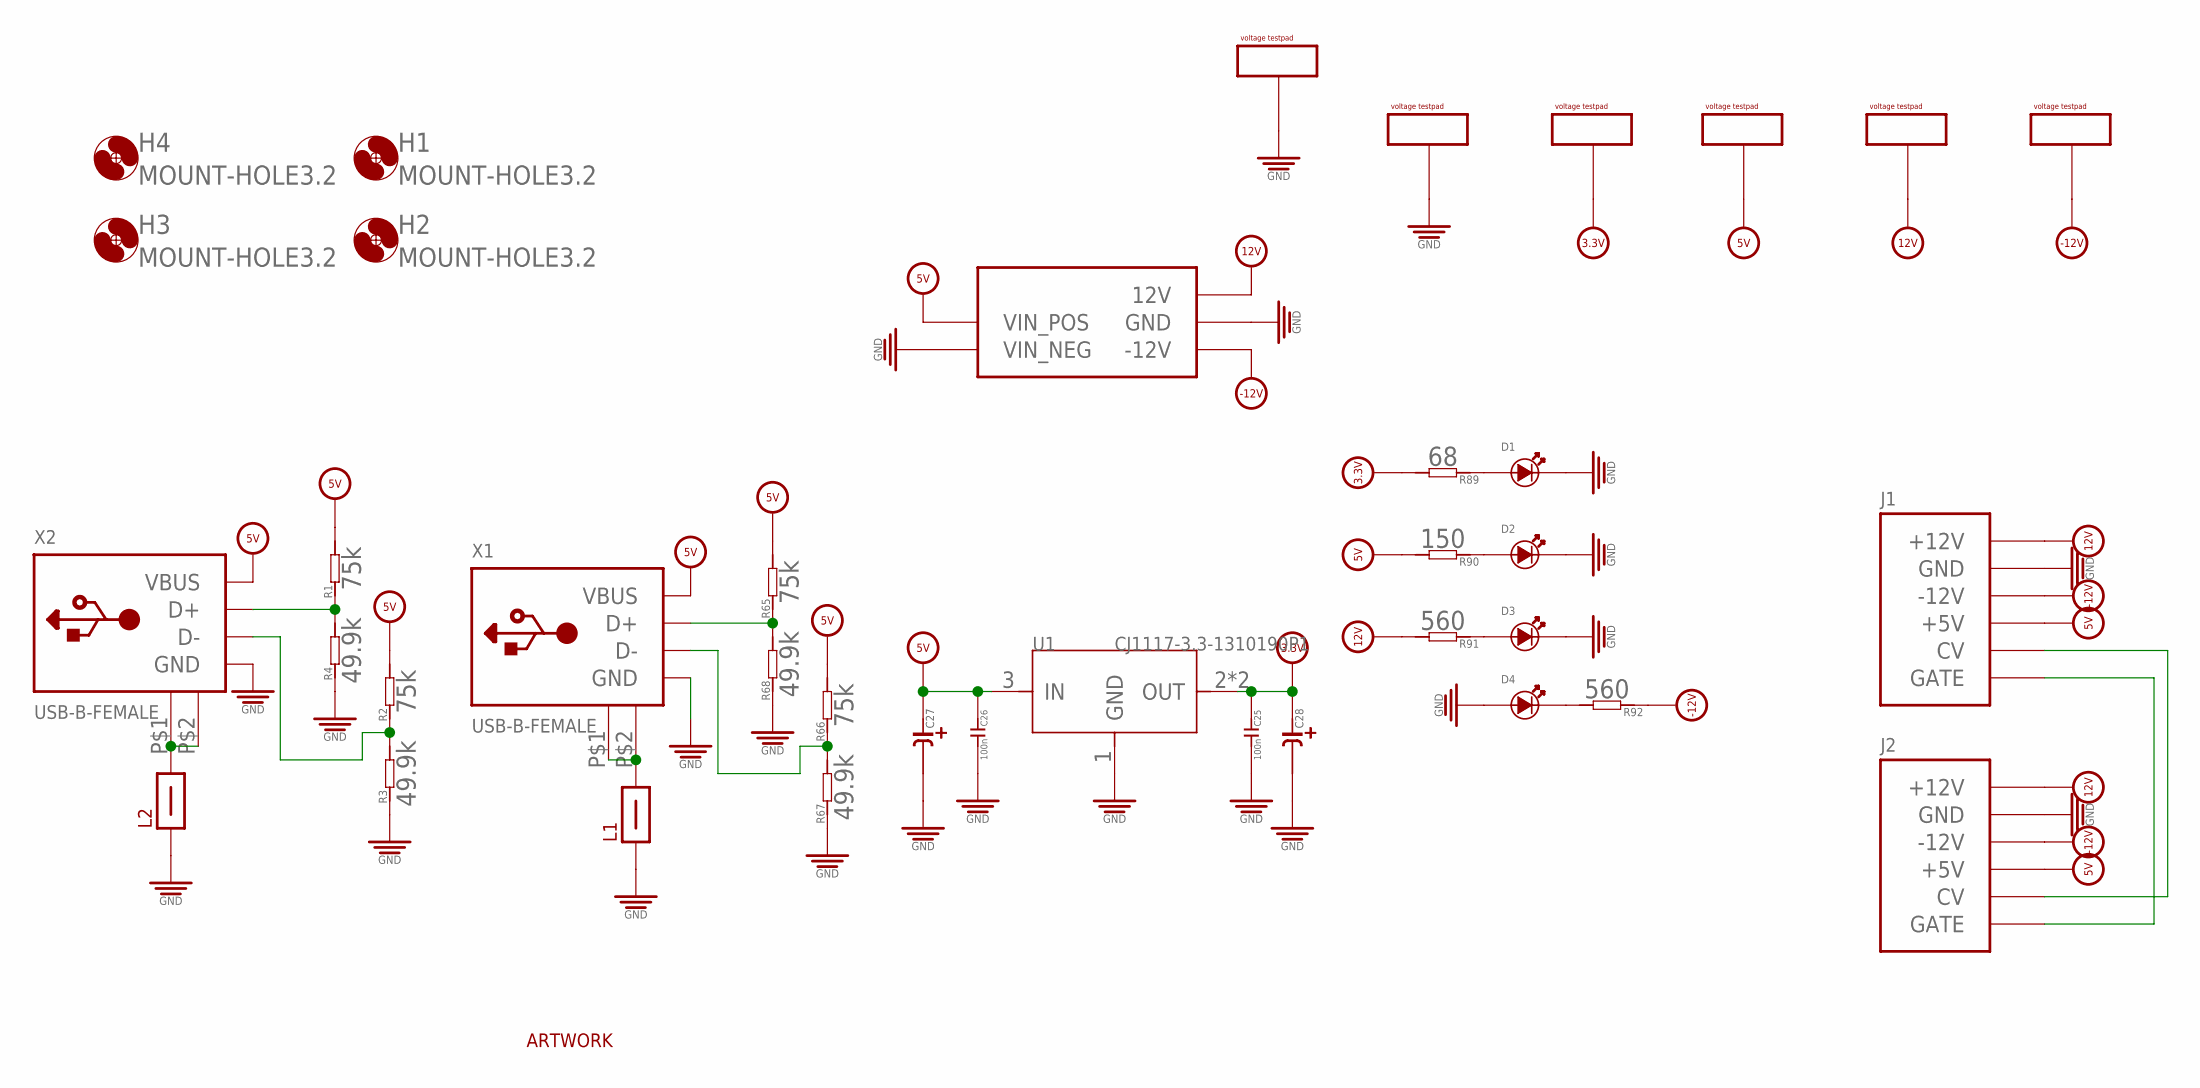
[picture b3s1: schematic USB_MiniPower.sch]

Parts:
C25, C26: 100n; C0603
C27, C28: C-POLAR-A; CASE-A_3216
D1, D2, D3, D4: LED; LED0603
H1, H2, H3, H4: MOUNT-HOLE3.2; 3,2
J1: POWER_SHROUDED_NOTEXT; POWER_16_SHROUDED_NOTEXT
J2: POWERSHROUDED; POWER_16_SHROUDED
L1, L2: FERRITE_1812
R1, R2, R65, R66: 75k; R0603
R3, R4, R67, R68: 49.9k; R0603
R89: 68; R0603
R90: 150; R0603
R91, R92: 560; R0603
U1: CJ1117-3.3-1310190P1; SOT223
U$7, U$8, U$9, U$10, U$11, U$16: VOLTAGETESTPAD_BIG; POWERTESTPAD_BIG
U$17: TINRS_ARTWORKTINYDATE; JUSTATINYROCKET_DATECODE
U$42: CINCONBRICK_12V; CINCONBRICK
X1, X2: USB-B-FEMALE; FCI61729

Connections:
3.3V: C25.1, C28.+ (1), R89.2, U1.2 (OUT), U1.TER (OUT), U$7.P$1, U$7.P$2, U$7.P$3
5V: C26.1, C27.+ (1), J1.11 (+5V), J1.12 (+5V), J2.11 (+5V), J2.12 (+5V), R1.2, R2.2, R65.2, R66.2, R90.2, U1.3 (IN), U$8.P$1, U$8.P$2, U$8.P$3, U$42.1 (VIN_POS), U$42.24 (VIN_POS), X1.1 (VBUS), X2.1 (VBUS)
12V: J1.9 (+12V), J1.10 (+12V), J2.9 (+12V), J2.10 (+12V), R91.2, U$9.P$1, U$9.P$2, U$9.P$3, U$42.11 (12V), U$42.14 (12V)
-12V: J1.1 (-12V), J1.2 (-12V), J2.1 (-12V), J2.2 (-12V), R92.1, U$10.P$1, U$10.P$2, U$10.P$3, U$42.2 (-12V), U$42.23 (-12V)
GND: C25.2, C26.2, C27.- (2), C28.- (2), D1.-, D2.-, D3.-, D4.+, J1.3 (GND), J1.4 (GND), J1.5 (GND), J1.6 (GND), J1.7 (GND), J1.8 (GND), J2.3 (GND), J2.4 (GND), J2.5 (GND), J2.6 (GND), J2.7 (GND), J2.8 (GND), L1.P$1, L2.P$1, R3.1, R4.1, R67.1, R68.1, U1.1 (GND), U$11.P$1, U$11.P$2, U$11.P$3, U$16.P$1, U$16.P$2, U$16.P$3, U$42.3 (GND), U$42.10 (GND), U$42.12 (VIN_NEG), U$42.13 (VIN_NEG), U$42.15 (GND), U$42.22 (GND), X1.4 (GND), X2.4 (GND)
unnamed: J1.13 (CV), J1.14 (CV), J2.13 (CV), J2.14 (CV)
unnamed: J1.15 (GATE), J1.16 (GATE), J2.15 (GATE), J2.16 (GATE)
unnamed: L2.P$2, X2.P$1 (GND1), X2.P$2 (GND2)
unnamed: L1.P$2, X1.P$1 (GND1), X1.P$2 (GND2)
unnamed: R66.1, R67.2, X1.2 (D-)
unnamed: R65.1, R68.2, X1.3 (D+)
unnamed: R2.1, R3.2, X2.2 (D-)
unnamed: R1.1, R4.2, X2.3 (D+)
unnamed: D1.+, R89.1
unnamed: D2.+, R90.1
unnamed: D3.+, R91.1
unnamed: D4.-, R92.2

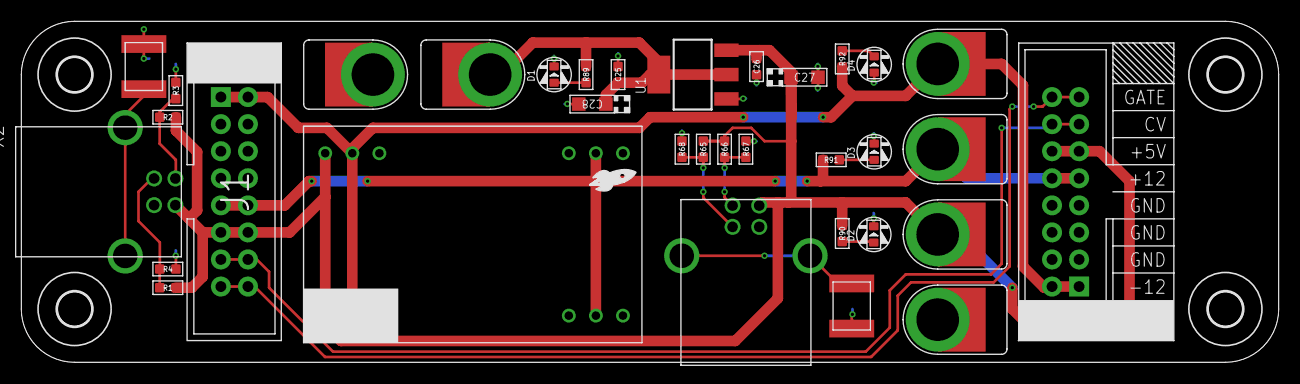
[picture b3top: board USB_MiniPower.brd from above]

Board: 2 copper layers, 118.0 x 32.0 mm, 39 parts (0 on the bottom side), 17 nets.

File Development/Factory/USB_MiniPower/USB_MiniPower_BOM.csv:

Comment,Designator,Footprint,LCSC Part #,combinedname,name
100n,"C25, C26",C0603,,C*_C0603_100n,C*
,"C27, C28",CASE-A_3216,,C-POLAR*_CASE-A_3216_,C-POLAR*
,"D1, D2, D3, D4",LED0603,,LED*_LED0603_,LED*
POWER_SHROUDED_NOTEXT,"J1",POWER_16_SHROUDED_NOTEXT,,POWER_POWER_16_SHROUDED_NOTEXT_POWER_SHROUDED_NOTEXT,POWER
POWERSHROUDED,"J2",POWER_16_SHROUDED,,POWER_POWER_16_SHROUDED_POWERSHROUDED,POWER
FERRITE_1812,"L1, L2",FERRITE_1812,,FERRITE_FERRITE_1812_FERRITE_1812,FERRITE
75k,"R65, R66, R1, R2",R0603,,R*_R0603_75k,R*
49.9k,"R67, R68, R3, R4",R0603,,R*_R0603_49.9k,R*
68,"R89",R0603,,R*_R0603_68,R*
150,"R90",R0603,,R*_R0603_150,R*
560,"R91, R92",R0603,,R*_R0603_560,R*
CINCONBRICK_12V,"U$42",CINCONBRICK,,CINCONBRICK_12V_CINCONBRICK_CINCONBRICK_12V,CINCONBRICK_12V
CJ1117-3.3-1310190P1,"U1",SOT223,,CJ1117-3.3_SOT223_CJ1117-3.3-1310190P1,CJ1117-3.3
USB-B-FEMALE,"X1, X2",FCI61729,,USB-B-FEMALE_FCI61729_USB-B-FEMALE,USB-B-FEMALE
VOLTAGETESTPAD_BIG,"U$7, U$8, U$9, U$10, U$11, U$16",POWERTESTPAD_BIG,,VOLTAGETESTPAD_POWERTESTPAD_BIG_VOLTAGETESTPAD_BIG,VOLTAGETESTPAD
MOUNT-HOLE3.2,"H1, H2, H3, H4",3,2,,MOUNT-HOLE_3.2_MOUNT-HOLE3.2,MOUNT-HOLE
TINRS_ARTWORKTINYDATE,"U$17",JUSTATINYROCKET_DATECODE,,TINRS_ARTWORK_JUSTATINYROCKET_DATECODE_TINRS_ARTWORKTINYDATE,TINRS_ARTWORK

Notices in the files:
parts and their libraries:
SparkFun-Aesthetics: Licensing: CC v3.0 Share-Alike You are welcome to use this library for commercial purposes.
